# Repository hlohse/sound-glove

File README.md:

# sound-glove
Sound Glove Master's thesis source code and hardware design

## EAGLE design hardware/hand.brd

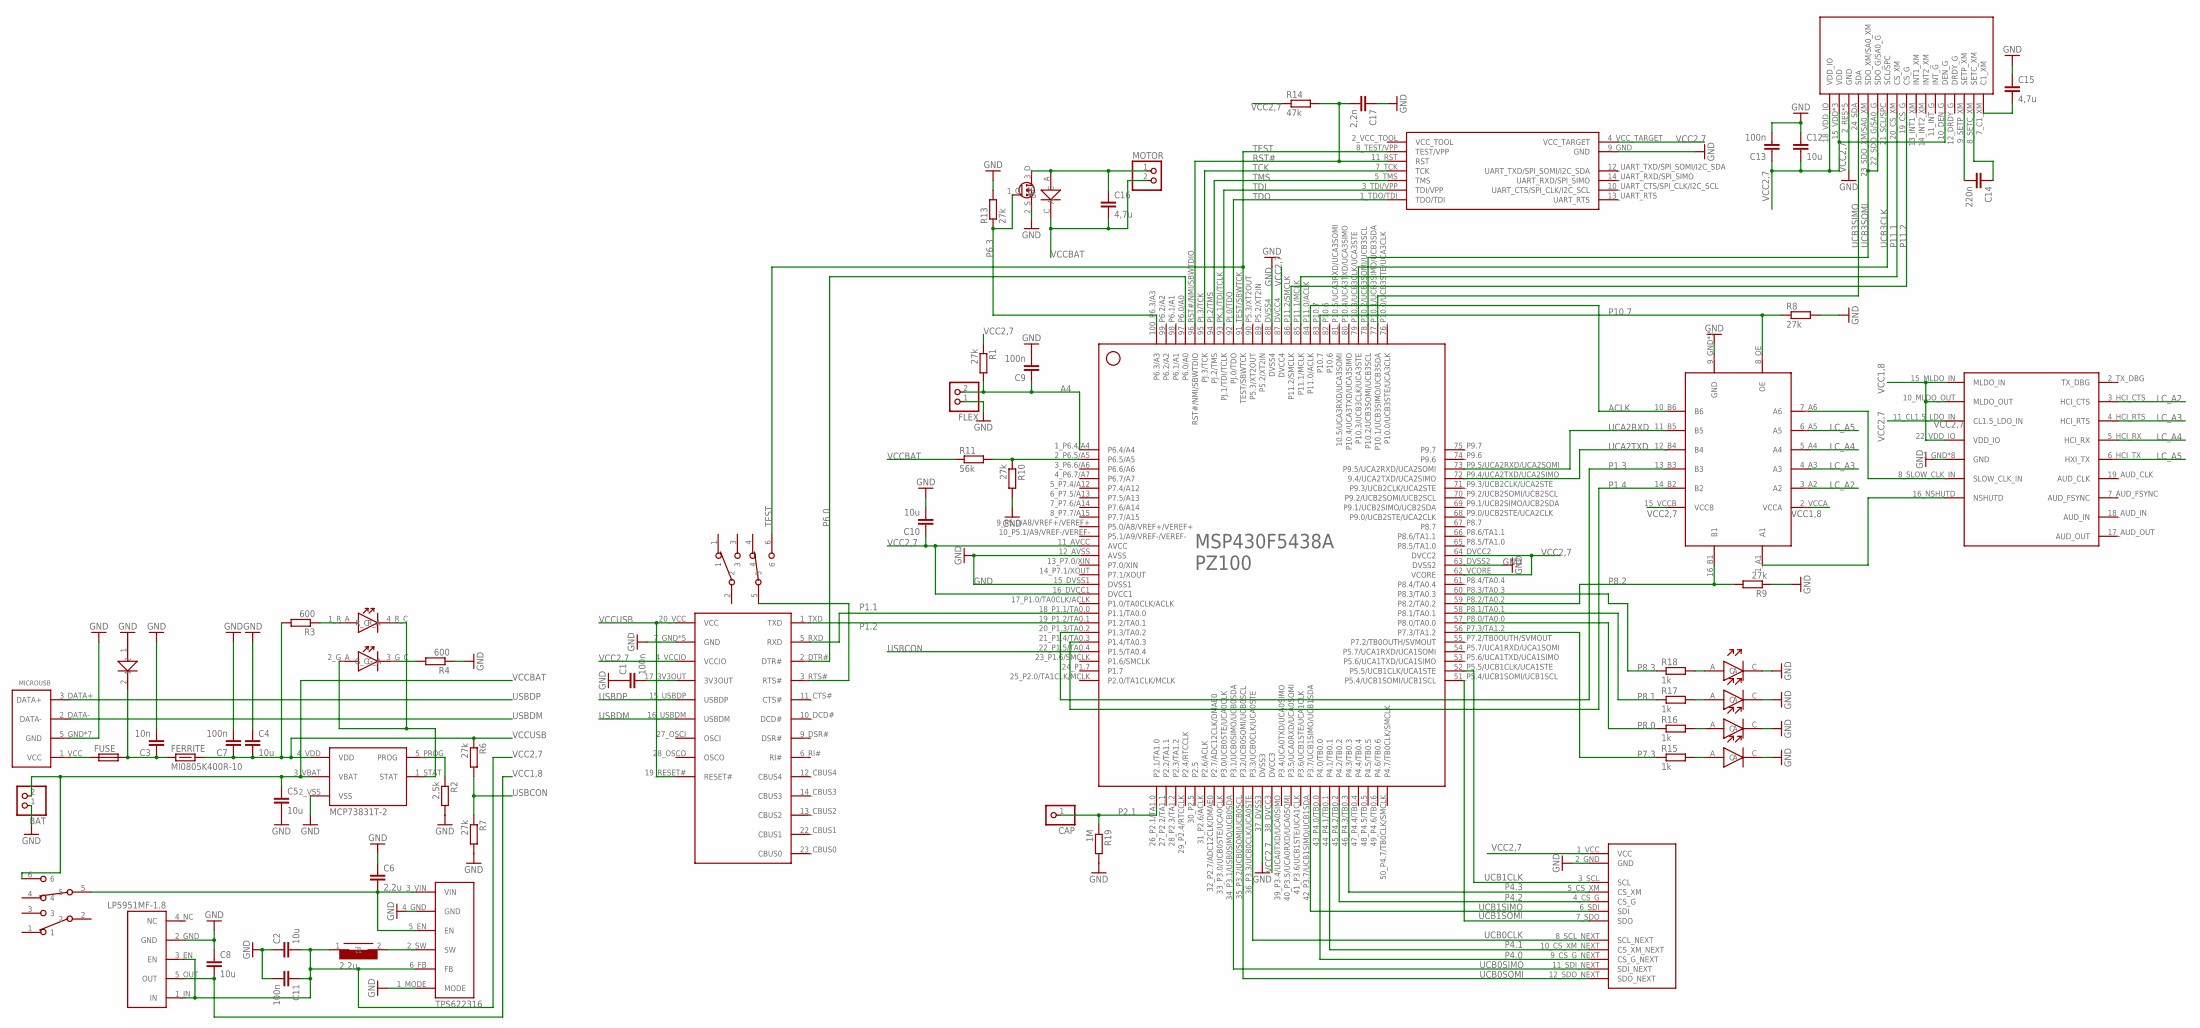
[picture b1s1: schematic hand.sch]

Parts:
BAT: 1X02
C1, C7, C9, C11, C13: 100n; C0402
C2, C4, C5, C8, C10, C12: 10u; C0805
C3: 10n; C0402
C6: 2,2u; C0805
C14: 220n; C0402
C15, C16: 4,7u; C0805
C17: 2,2n; C0603
CAP: 1X01
FERRITE: MI0805K400R-10; R0603
FLEX: 1X02
FUSE: SICHERUNG; C0603
IMU_OUT: IMU-BUCHSE-OUT; OUT
LP5951MF-1.8: VDDIOREGLER-SC70; SC70
MCP73831T-2: MCP73831/2-SOT-23-5; SOT-23-5
MICROUSB: MICRO_USB-PCB; PCB
MOTOR: 1X02
R1, R6, R7, R8, R9, R10, R13: 27k; R0402
R2: 2,5k; R0402
R3, R4: 600; R0402
R11: 56k; R0402
R14: 47k; R0402
R15, R16, R17, R18: 1k; R0402
R19: 1M; R0402
SPULE: 2,2u; C0603
TPS622316: SCHALTREGLER-R-PUSON-N6; R-PUSON-N6
U$1: FT232R-SSOP-28; SSOP-28
U$2: LSM9DS0-LGA-24; LGA-24
U$4: PAN132X; BOARD
U$5: MSP430BT5190-PZ100; PZ100
U$7: LED-PCB; PCB
U$8: LADE-MOSFET-SOC-23; SOT-23
U$9: FREILAUFDIODE; FEILAUFDIODE
U$11, U$12: ANSCHALTER-PACKAGE; PACKAGE
U$13: LOGIKPEGELWANDLER-6CH; R-PVQFN-N16
U$15, U$17, U$18, U$19: LEDMINI
U$16: JTAG-BUCHSE; BUCHSE
U$20: DIODE-C0603; C0603

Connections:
A4: C9.1, FLEX.2, R1.2, U$5.1_P6.4/A4 (P6.4/A4)
ACLK: U$5.84_P11.0/ACLK (P11.0/ACLK), U$13.10_B6 (B6)
GND: BAT.1, C1.1, C2.1, C3.2, C4.1, C5.2, C6.1, C7.2, C8.1, C9.2, C10.2, C11.2, C12.1, C13.2, C15.1, C17.1, FLEX.1, IMU_OUT.2_GND (GND), LP5951MF-1.8.2_GND (GND), MCP73831T-2.2_VSS (VSS), MICROUSB.5_GND (GND), MICROUSB.EP_1 (GND), MICROUSB.EP_2 (GND), MICROUSB.EP_3 (GND), MICROUSB.EP_4 (GND), MICROUSB.P$1 (GND), MICROUSB.P$2 (GND), R2.2, R4.1, R7.2, R8.2, R9.1, R10.2, R13.2, R19.2, TPS622316.1_MODE (MODE), TPS622316.4_GND (GND), U$1.7_GND (GND), U$1.18_GND (GND), U$1.21_GND (GND), U$1.25_AGND (GND), U$1.26_TEST (GND), U$2.2_RES (GND), U$2.3_RES (GND), U$2.4_RES (GND), U$2.5_GND (GND), U$2.6_GND (GND), U$4.1_GND (GND), U$4.12_GND (GND), U$4.14_GND (GND), U$4.20_GND (GND), U$4.A_GND (GND), U$4.B_GND (GND), U$4.C_GND (GND), U$4.D_GND (GND), U$5.12_AVSS (AVSS), U$5.15_DVSS1 (DVSS1), U$5.37_DVSS3 (DVSS3), U$5.63_DVSS2 (DVSS2), U$5.88_DVSS4 (DVSS4), U$8.2_S (S), U$13.9_GND (GND), U$13.PAD (GND), U$15.C, U$16.9_GND (GND), U$17.C, U$18.C, U$19.C, U$20.1
LC_A2: U$4.3_HCI_CTS (HCI_CTS), U$13.3_A2 (A2)
LC_A3: U$4.4_HCI_RTS (HCI_RTS), U$13.4_A3 (A3)
LC_A4: U$4.5_HCI_RX (HCI_RX), U$13.5_A4 (A4)
LC_A5: U$4.6_HCI_TX (HXI_TX), U$13.6_A5 (A5)
unnamed: U$1.3_RTS# (RTS#), U$11.5
unnamed: C3.1, FERRITE.1, FUSE.2, U$20.2
unnamed: C1.2, U$1.17_3V3OUT (3V3OUT)
unnamed: R10.1, R11.2, U$5.2_P6.5/A5 (P6.5/A5)
unnamed: MCP73831T-2.5_PROG (PROG), R2.1
unnamed: R3.1, U$7.1_R_A (R_A)
unnamed: MCP73831T-2.1_STAT (STAT), U$7.2_G_A (G_A), U$7.4_R_C (R_C)
unnamed: U$4.8_SLOW_CLK_IN (SLOW_CLK_IN), U$13.7_A6 (A6)
unnamed: R4.2, U$7.3_G_C (G_C)
unnamed: SPULE.2, TPS622316.2_SW (SW)
unnamed: C6.2, TPS622316.3_VIN (VIN), TPS622316.5_EN (EN), U$12.5
unnamed: U$4.16_NSHUTD (NSHUTD), U$13.1_A1 (A1)
unnamed: C16.1, MOTOR.1, U$8.3_D (D), U$9.A
unnamed: R18.2, U$15.A
unnamed: C15.2, U$2.7_C1_XM (C1_XM)
unnamed: C14.1, U$2.8_SETC_XM (SETC_XM)
unnamed: C14.2, U$2.9_SETP_XM (SETP_XM)
unnamed: R17.2, U$17.A
unnamed: R16.2, U$18.A
unnamed: R15.2, U$19.A
unnamed: FUSE.1, MICROUSB.1_VCC (VCC)
P1.1: U$1.5_RXD (RXD), U$5.18_P1.1/TA0.0 (P1.1/TA0.0)
P1.2: U$1.1_TXD (TXD), U$5.19_P1.2/TA0.1 (P1.2/TA0.1)
P1.3: U$5.20_P1.3/TA0.2 (P1.3/TA0.2), U$13.13_B3 (B3)
P1.4: U$5.21_P1.4/TA0.3 (P1.4/TA0.3), U$13.14_B2 (B2)
P2.1: CAP.1, R19.1, U$5.26_P2.1/TA1.0 (P2.1/TA1.0)
P4.0: IMU_OUT.9_CS_G_NEXT (CS_G_NEXT), U$5.43_P4.0/TB0.0 (P4.0/TB0.0)
P4.1: IMU_OUT.10_CS_XM_NEXT (CS_XM_NEXT), U$5.44_P4.1/TB0.1 (P4.1/TB0.1)
P4.2: IMU_OUT.4_CS_G (CS_G), U$5.45_P4.2/TB0.2 (P4.2/TB0.2)
P4.3: IMU_OUT.5_CS_XM (CS_XM), U$5.46_P4.3/TB0.3 (P4.3/TB0.3)
P6.0: U$1.2_DTR# (DTR#), U$5.97_P6.0/A0 (P6.0/A0)
P6.3: R13.1, U$5.100_P6.3/A3 (P6.3/A3), U$8.1_G (G)
P7.3: R15.1, U$5.56_P7.3/TA1.2 (P7.3/TA1.2)
P8.0: R16.1, U$5.57_P8.0/TA0.0 (P8.0/TA0.0)
P8.1: R17.1, U$5.58_P8.1/TA0.1 (P8.1/TA0.1)
P8.2: R9.2, U$5.59_P8.2/TA0.2 (P8.2/TA0.2), U$13.16_B1 (B1)
P8.3: R18.1, U$5.60_P8.3/TA0.3 (P8.3/TA0.3)
P10.7: R8.1, U$5.83_P10.7 (P10.7), U$13.8_OE (OE)
P11.1: U$2.20_CS_XM (CS_XM), U$5.85_P11.1/MCLK (P11.1/MCLK)
P11.2: U$2.19_CS_G (CS_G), U$5.86_P11.2/SMCLK (P11.2/SMCLK)
RST#: C17.2, R14.2, U$5.96_RST#/NMI/SBWTDIO (RST#/NMI/SBWTDIO), U$16.11_RST (RST)
TCK: U$5.95_PJ.3/TCK (PJ.3/TCK), U$16.7_TCK (TCK)
TDI: U$5.93_PK.1/TDI/TCLK (PJ.1/TDI/TCLK), U$16.3_TDI/VPP (TDI/VPP)
TDO: U$5.92_PJ.0/TDO (PJ.0/TDO), U$16.1_TDO/TDI (TDO/TDI)
TEST: U$5.91_TEST/SBWTCK (TEST/SBWTCK), U$11.6, U$16.8_TEST/VPP (TEST/VPP)
TMS: U$5.94_PJ.2/TMS (PJ.2/TMS), U$16.5_TMS (TMS)
UCA2RXD: U$5.73_P9.5/UCA2RXD/UCA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 (P9.5/UCA2RXD/UCA2SOMI), U$13.11_B5 (B5)
UCA2TXD: U$5.72_P9.4/UCA2TXD/UCA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 (9.4/UCA2TXD/UCA2SIMO), U$13.12_B4 (B4)
UCB0CLK: IMU_OUT.8_SCL_NEXT (SCL_NEXT), U$5.36_P3.3/UCB0CLK/UCA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 (P3.3/UCB0CLK/UCA0STE)
UCB0SIMO: IMU_OUT.11_SDI_NEXT (SDI_NEXT), U$5.34_P3.1/USB0SIMO/UC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 (P3.1/UCB0SIMO/UCB0SDA)
UCB0SOMI: IMU_OUT.12_SDO_NEXT (SDO_NEXT), U$5.35_P3.2/UCB0SOMI/UC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 (P3.2/UCB0SOMI/UCB0SCL)
UCB1CLK: IMU_OUT.3_SCL (SCL), U$5.52_P5.5/UCB1CLK/UCA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 (P5.5/UCB1CLK/UCA1STE)
UCB1SIMO: IMU_OUT.6_SDI (SDI), U$5.42_P3.7/UCB1SIMO/UC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 (P3.7/UCB1SIMO/UCB1SDA)
UCB1SOMI: IMU_OUT.7_SDO (SDO), U$5.51_P5.4/UCB1SOMI/UC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 (P5.4/UCB1SOMI/UCB1SCL)
UCB3CLK: U$2.21_SCL/SPC (SCL/SPC), U$5.79_P10.3/UCB3CLK/UC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 (P10.3/UCB3CLK/UCA3STE)
UCB3SIMO: U$2.24_SDA (SDA), U$5.77_P10.1/UCB3SIMO/U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 (P10.1/UCB3SIMO/UCB3SDA)
UCB3SOMI: U$2.22_SDO_G/SA0_G (SDO_G/SA0_G), U$2.23_SDO_XM/SA0_XM (SDO_XM/SA0_XM), U$5.78_P10.2/UCB3SOMI/U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 (P10.2/UCB3SOMI/UCB3SCL)
USBCON: R6.2, R7.1, U$5.22_P1.5/TA0.4 (P1.5/TA0.4)
USBDM: MICROUSB.2_DATA- (DATA-), U$1.16_USBDM (USBDM)
USBDP: MICROUSB.3_DATA+ (DATA+), U$1.15_USBDP (USBDP)
VCC1,8: C8.2, LP5951MF-1.8.5_OUT (OUT), U$4.10_MLDO_OUT (MLDO_OUT), U$4.15_MLDO_IN (MLDO_IN), U$4.22_VDD_IO (VDD_IO), U$13.2_VCCA (VCCA)
VCC2,7: C2.2, C10.1, C11.1, C12.2, C13.1, IMU_OUT.1_VCC (VCC), LP5951MF-1.8.1_IN (IN), LP5951MF-1.8.3_EN (EN), R1.1, R14.1, SPULE.1, TPS622316.6_FB (FB), U$1.4_VCCIO (VCCIO), U$2.10_DEN_G (DEN_G), U$2.15_VDD (VDD), U$2.16_VDD (VDD), U$2.17_VDD (VDD), U$2.18_VDD_IO (VDD_IO), U$4.11_CL1.5_LDO_IN (CL1.5_LDO_IN), U$5.11_AVCC (AVCC), U$5.16_DVCC1 (DVCC1), U$5.38_DVCC3 (DVCC3), U$5.62_VCORE (VCORE), U$5.64_DVCC2 (DVCC2), U$5.87_DVCC4 (DVCC4), U$13.15_VCCB (VCCB), U$16.4_VCC_TARGET (VCC_TARGET)
VCCBAT: BAT.2, C5.1, C16.2, MCP73831T-2.3_VBAT (VBAT), MOTOR.2, R11.1, U$9.C, U$12.6
VCCUSB: C4.2, C7.1, FERRITE.2, MCP73831T-2.4_VDD (VDD), R3.2, R6.1, U$1.19_RESET# (RESET#), U$1.20_VCC (VCC)

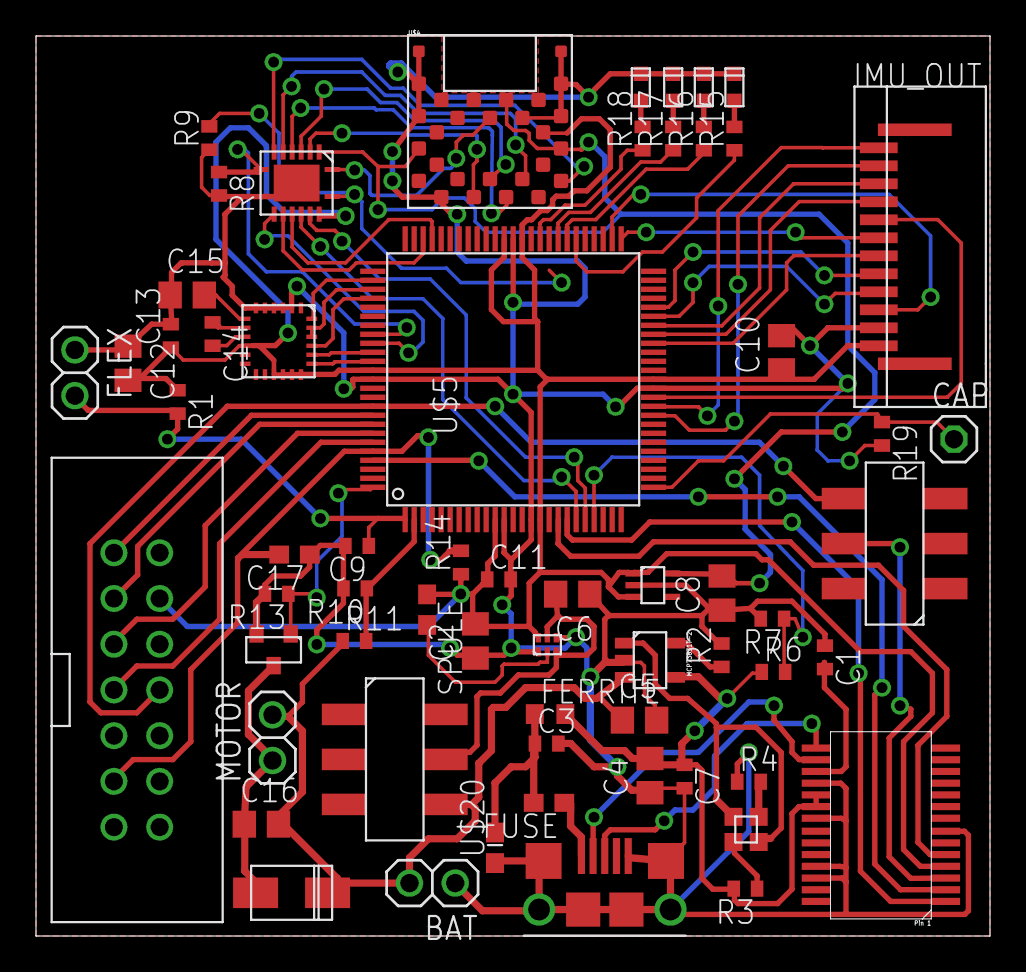
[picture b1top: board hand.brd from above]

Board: 2 copper layers, 53.0 x 50.0 mm, 62 parts (0 on the bottom side), 71 nets.

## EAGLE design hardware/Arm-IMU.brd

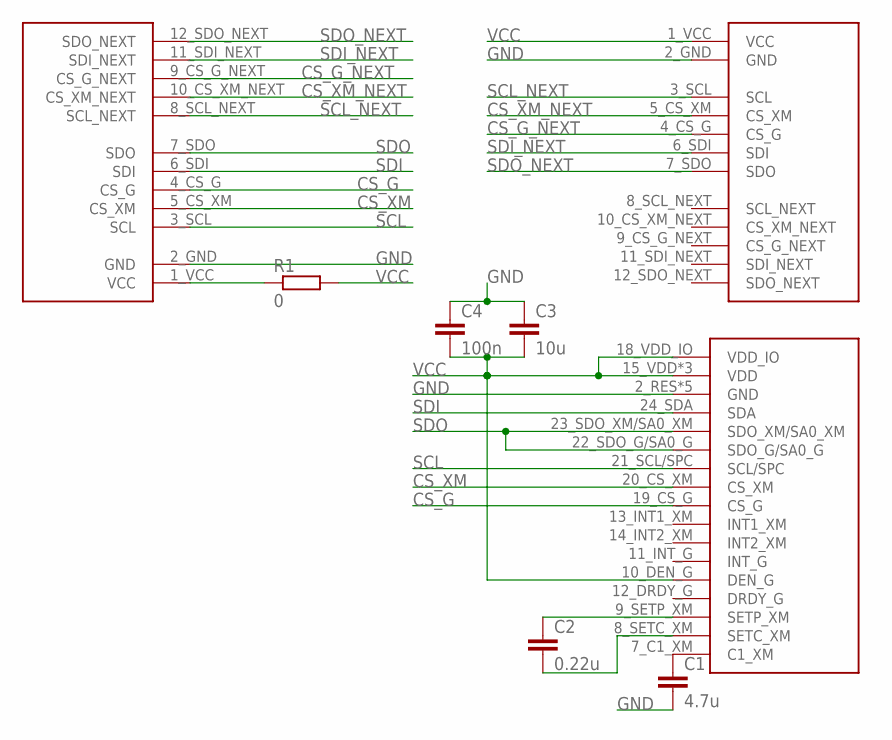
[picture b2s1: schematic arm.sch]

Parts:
C1: 4.7u; C0805
C2: 0.22u; C0805
C3: 10u; C0805
C4: 100n; C0603
IMU_IN: IMU-BUCHSE-IN; IN
IMU_OUT: IMU-BUCHSE-OUT; OUT
R1: 0; R0402
U$1: LSM9DS0-LGA-24; LGA-24

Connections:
CS_G: IMU_IN.4_CS_G (CS_G), U$1.19_CS_G (CS_G)
CS_G_NEXT: IMU_IN.9_CS_G_NEXT (CS_G_NEXT), IMU_OUT.4_CS_G (CS_G)
CS_XM: IMU_IN.5_CS_XM (CS_XM), U$1.20_CS_XM (CS_XM)
CS_XM_NEXT: IMU_IN.10_CS_XM_NEXT (CS_XM_NEXT), IMU_OUT.5_CS_XM (CS_XM)
GND: C1.2, C3.1, C4.1, IMU_IN.2_GND (GND), IMU_OUT.2_GND (GND), U$1.2_RES (GND), U$1.3_RES (GND), U$1.4_RES (GND), U$1.5_GND (GND), U$1.6_GND (GND)
unnamed: C1.1, U$1.7_C1_XM (C1_XM)
unnamed: C2.1, U$1.9_SETP_XM (SETP_XM)
unnamed: C2.2, U$1.8_SETC_XM (SETC_XM)
unnamed: IMU_IN.1_VCC (VCC), R1.1
SCL: IMU_IN.3_SCL (SCL), U$1.21_SCL/SPC (SCL/SPC)
SCL_NEXT: IMU_IN.8_SCL_NEXT (SCL_NEXT), IMU_OUT.3_SCL (SCL)
SDI: IMU_IN.6_SDI (SDI), U$1.24_SDA (SDA)
SDI_NEXT: IMU_IN.11_SDI_NEXT (SDI_NEXT), IMU_OUT.6_SDI (SDI)
SDO: IMU_IN.7_SDO (SDO), U$1.22_SDO_G/SA0_G (SDO_G/SA0_G), U$1.23_SDO_XM/SA0_XM (SDO_XM/SA0_XM)
SDO_NEXT: IMU_IN.12_SDO_NEXT (SDO_NEXT), IMU_OUT.7_SDO (SDO)
VCC: C3.2, C4.2, IMU_OUT.1_VCC (VCC), R1.2, U$1.10_DEN_G (DEN_G), U$1.15_VDD (VDD), U$1.16_VDD (VDD), U$1.17_VDD (VDD), U$1.18_VDD_IO (VDD_IO)

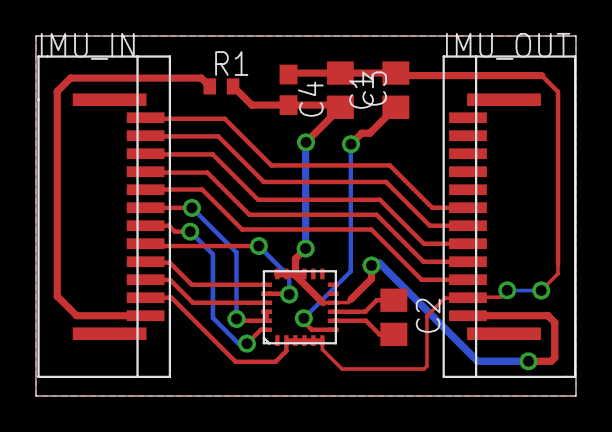
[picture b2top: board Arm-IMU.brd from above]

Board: 2 copper layers, 30.0 x 20.0 mm, 8 parts (0 on the bottom side), 16 nets.

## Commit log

2015-08-23 Transferred source code and hardware design files from private Bitbucket development repository
2015-08-23 Transferred thesis data, matlab and gnupot scripts from private Bitbucket development repository
2015-08-23 Renamed hardware design files
2015-08-23 Added thesis
2015-09-03 Changed Vector include guard to be standard-compliant. Fixes firmware compilation error that is non-existent in the previous repository.
